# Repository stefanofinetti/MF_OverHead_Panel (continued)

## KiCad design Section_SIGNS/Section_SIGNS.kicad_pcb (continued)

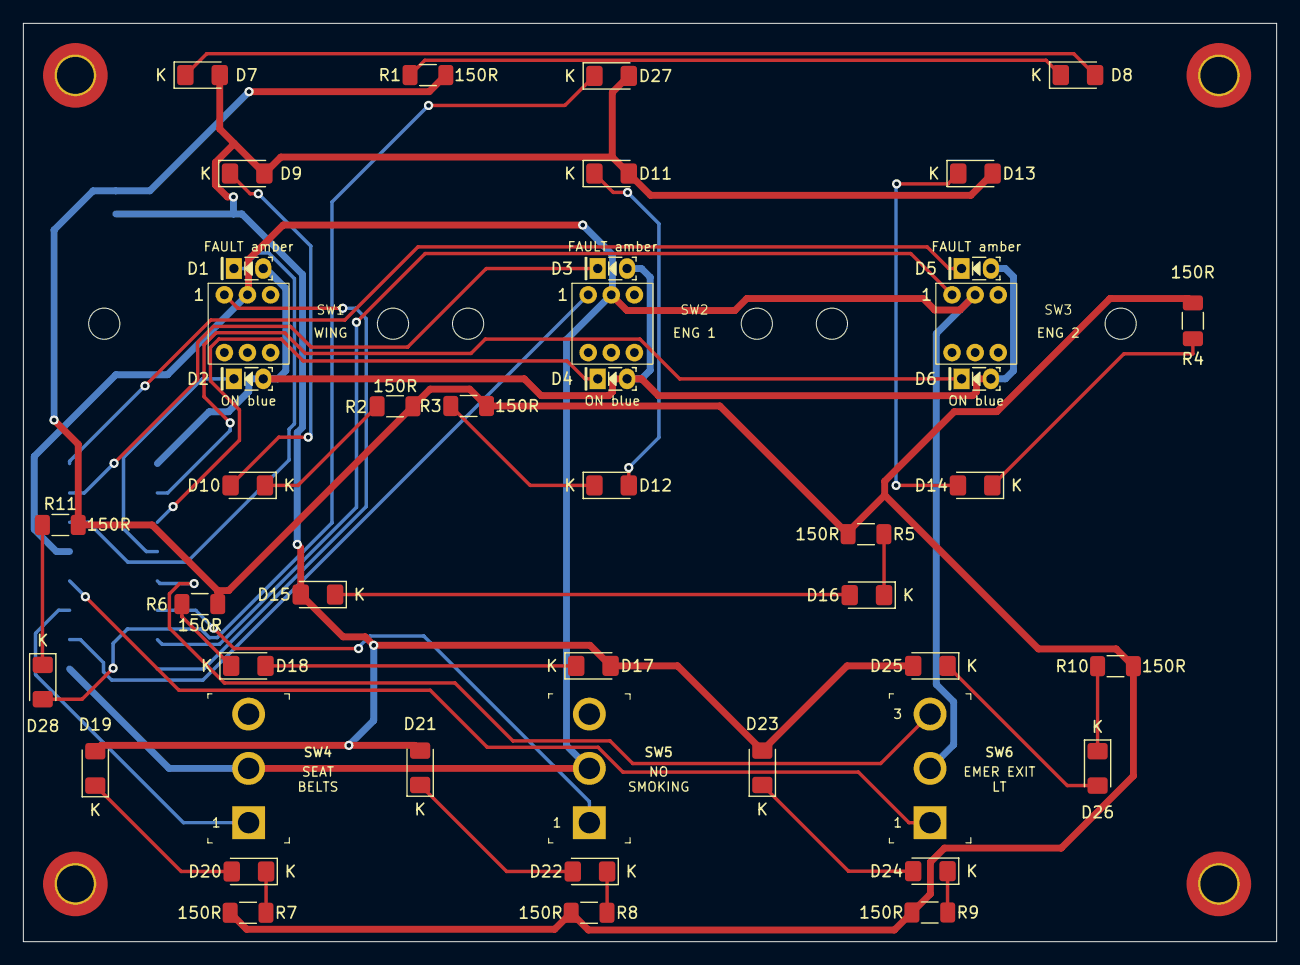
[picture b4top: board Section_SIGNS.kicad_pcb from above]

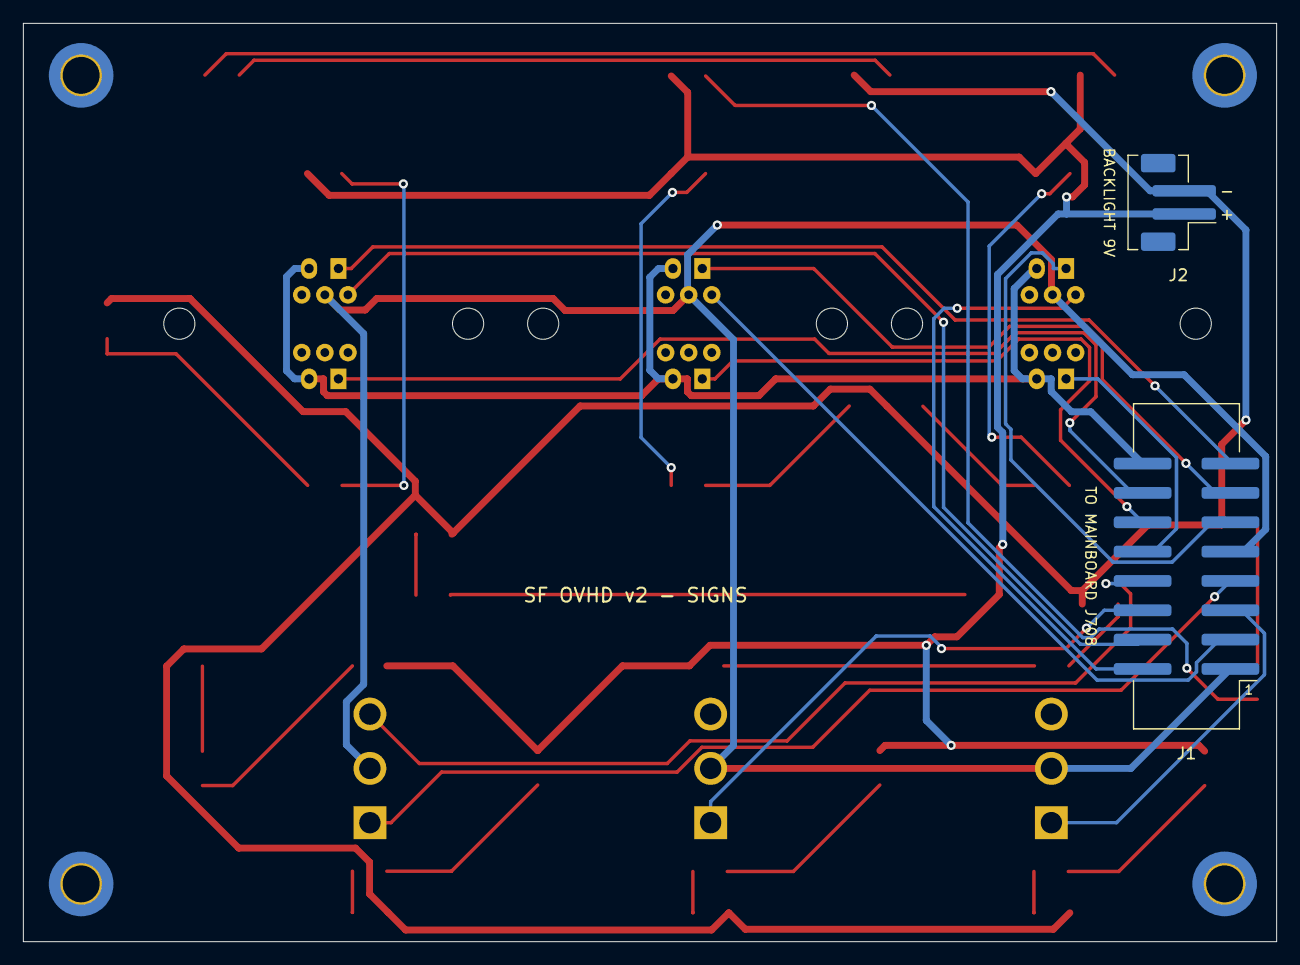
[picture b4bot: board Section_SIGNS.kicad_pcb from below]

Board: 2 copper layers, 108.5 x 79.5 mm, 57 parts (2 on the bottom side), 39 nets.

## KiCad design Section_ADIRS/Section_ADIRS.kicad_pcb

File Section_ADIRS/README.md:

# ADIRS section board (v2)

The v2 board under the ADIRS panel. It carries the panel's switches, annunciator LEDs and backlight, at their v1 positions, and reaches the mainboard through one ribbon and one pair of backlight wires. There are no ICs on it. The design rules shared by the eight section boards are in [`docs/board-split.md`](../docs/board-split.md).

* **PCB:** 132.5 × 81.5 mm, 2 layers, 1.6 mm. Every v1 hole is kept.
* **Status:** routed with Freerouting. ERC, DRC and schematic parity are clean. Not yet ordered.

**Top**, the panel side:

**Bottom**, with the connectors:

Rendered by KiCad from the board file. The bottom is seen from below, so it is mirrored against the top. The ADR rotaries have no 3D model yet and show as pads only.

## Connectors

Both are new on v2 and sit on the **back**, so nothing new stands proud of the front.

| Ref | What | Goes to |
|---|---|---|
| J1 | Shrouded IDC header, 20 pins, SMD | J701 on the mainboard, straight ribbon, pin 1 to pin 1 |
| J2 | JST PH, 2 pins, SMD. Pin 1 `+9V_BL` (`+`), pin 2 the switched return (`−`) | screw terminal J601 on the mainboard |

J1 and J2 are on the back between ADR 1 and ADR 3.

The signal on every ribbon pin is in the design document: [ADIRS — 20 pins](../docs/board-split.md#adirs--20-pins).

## Switches

| Ref | Switch | Type | v1 ref |
|---|---|---|---|
| SW1 | ADIRS ADR 1 | ADR rotary | SW25 |
| SW2 | ADIRS ADR 3 | ADR rotary | SW26 |
| SW3 | ADIRS ADR 2 | ADR rotary | SW27 |
| SW4 | ADIRS GND CTL | Korry | SW24 |

## Annunciators

Anodes on `+5V_LED` from the ribbon, cathodes back down the ribbon to their TLC5927 output. No resistors: the TLC5927 sets the current.

| Ref | Colour | Legend | Chain bit | Driver | v1 ref |
|---|---|---|---|---|---|
| D1 | blue | `GND_CTL_ON` | `ANN_LOWER` 16 | U502 (v1 U7) | D109 |

## Backlight

18 LEDs, 1206 (D2–D19), on 9 V, in 9 strings of two with 150 Ω (R1–R9). Each string runs at about 17 mA. `K` marks every cathode on the silkscreen.

## Assembly notes

* **SW2, in the middle, is IR 3, and SW3, on the right, is IR 2**, as on the A320 (IR 1, IR 3, IR 2 from left to right) and in the `.mfmc`. The v1 footprints were labelled the other way round; the copper decides.
* Rotary positions: 1 OFF, 2 NAV, 3 ATT; common on pin 9, to GND.
* J3 is the ADIRS OLED socket, where it was on v1: 1 GND, 2 +3V3, 3 SCL, 4 SDA, on PCA9548A channel 2.
* GND CTL is on this board because that is where it sits under the printed panel.
* There is no 3D model of the ADR rotary yet, so the render shows only its pads.
* Every part has its value, polarity or pin 1 on the silkscreen of its own side. Each part's description in the schematic names its v1 reference.

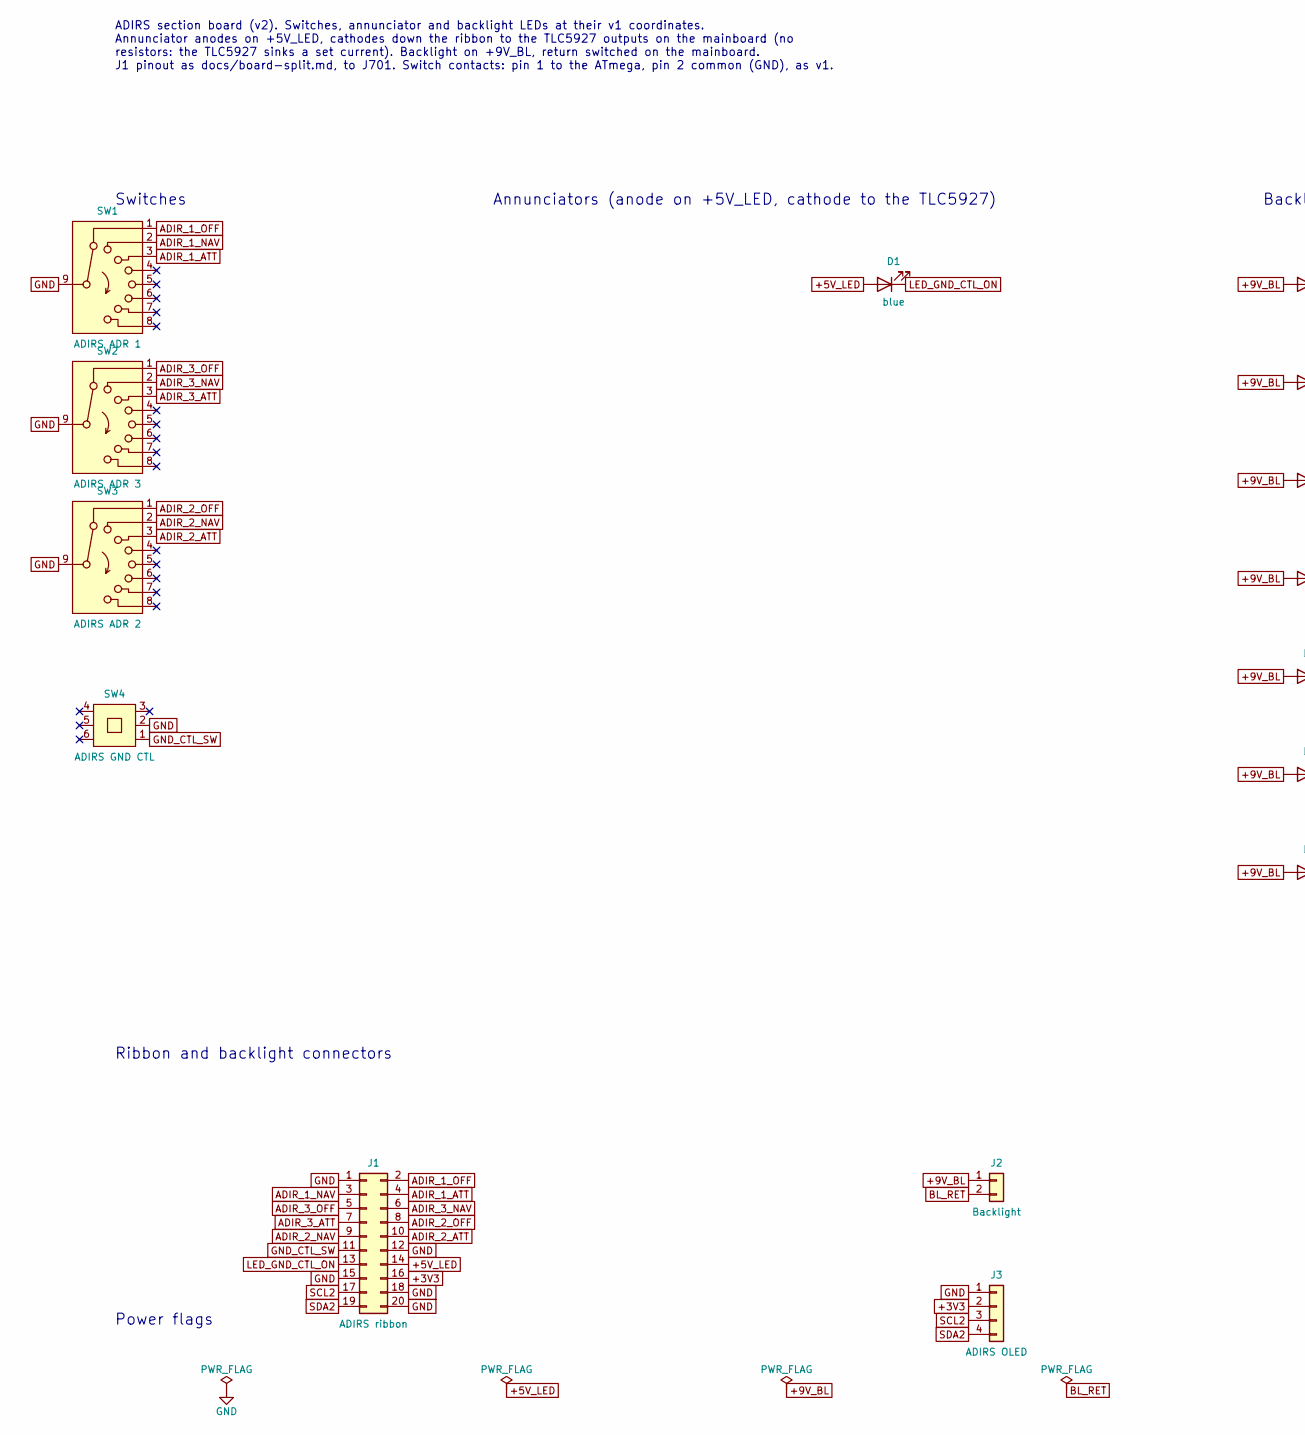
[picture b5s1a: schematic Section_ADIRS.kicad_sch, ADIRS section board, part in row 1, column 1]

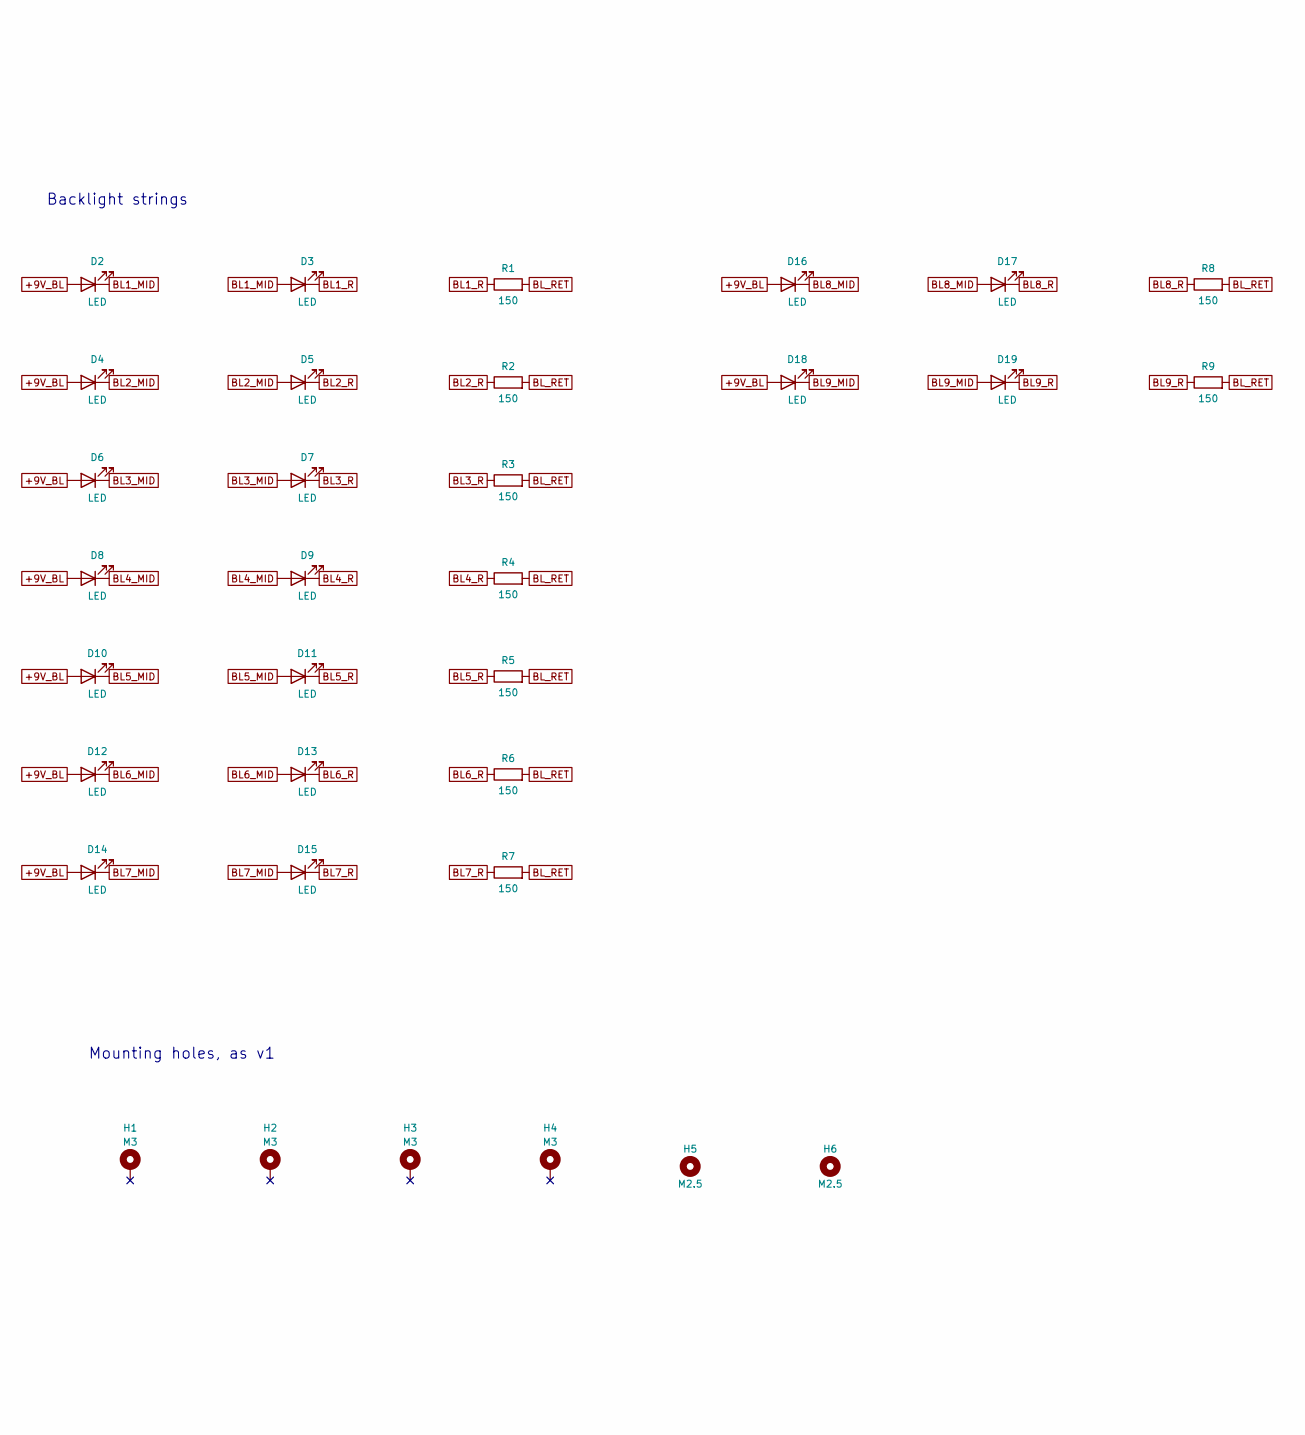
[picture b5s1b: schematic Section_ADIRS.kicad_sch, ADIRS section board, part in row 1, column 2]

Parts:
D1: blue; LED_Rectangular_W3.9mm_H1.8mm_FlatTop
D2, D3, D4, D5, D6, D7, D8, D9, D10, D11, D12, D13, D14, D15, D16, D17, D18, D19: LED; LED_1206_3216Metric_Pad1.42x1.75mm_HandSolder
H1, H2, H3, H4: M3; MountingHole_3.2mm_M3_DIN965_Pad_TopBottom
H5, H6: M2.5; MountingHole_2.7mm_M2.5
J1: ADIRS ribbon; IDC-Header_2x10_P2.54mm_Vertical_SMD
J2: Backlight; JST_PH_B2B-PH-SM4-TB_1x02-1MP_P2.00mm_Vertical
J3: ADIRS OLED; PinSocket_1x04_P2.54mm_Vertical
R1, R2, R3, R4, R5, R6, R7, R8, R9: 150; R_1206_3216Metric_Pad1.30x1.75mm_HandSolder
SW1: ADIRS ADR 1; Rotary_SW_8x1_SF
SW2: ADIRS ADR 3; Rotary_SW_8x1_SF
SW3: ADIRS ADR 2; Rotary_SW_8x1_SF
SW4: ADIRS GND CTL; G-Switch_PS-7054DVB-6PN

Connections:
+3V3: J1.16, J3.2
+5V_LED: D1.2 (A), J1.14
+9V_BL: D2.2 (A), D4.2 (A), D6.2 (A), D8.2 (A), D10.2 (A), D12.2 (A), D14.2 (A), D16.2 (A), D18.2 (A), J2.1
ADIR_1_ATT: J1.4, SW1.3
ADIR_1_NAV: J1.3, SW1.2
ADIR_1_OFF: J1.2, SW1.1
ADIR_2_ATT: J1.10, SW3.3
ADIR_2_NAV: J1.9, SW3.2
ADIR_2_OFF: J1.8, SW3.1
ADIR_3_ATT: J1.7, SW2.3
ADIR_3_NAV: J1.6, SW2.2
ADIR_3_OFF: J1.5, SW2.1
BL1_MID: D2.1 (K), D3.2 (A)
BL1_R: D3.1 (K), R1.1
BL2_MID: D4.1 (K), D5.2 (A)
BL2_R: D5.1 (K), R2.1
BL3_MID: D6.1 (K), D7.2 (A)
BL3_R: D7.1 (K), R3.1
BL4_MID: D8.1 (K), D9.2 (A)
BL4_R: D9.1 (K), R4.1
BL5_MID: D10.1 (K), D11.2 (A)
BL5_R: D11.1 (K), R5.1
BL6_MID: D12.1 (K), D13.2 (A)
BL6_R: D13.1 (K), R6.1
BL7_MID: D14.1 (K), D15.2 (A)
BL7_R: D15.1 (K), R7.1
BL8_MID: D16.1 (K), D17.2 (A)
BL8_R: D17.1 (K), R8.1
BL9_MID: D18.1 (K), D19.2 (A)
BL9_R: D19.1 (K), R9.1
BL_RET: J2.2, R1.2, R2.2, R3.2, R4.2, R5.2, R6.2, R7.2, R8.2, R9.2
GND: J1.1, J1.12, J1.15, J1.18, J1.20, J3.1, SW1.9, SW2.9, SW3.9, SW4.2
GND_CTL_SW: J1.11, SW4.1
LED_GND_CTL_ON: D1.1 (K), J1.13
SCL2: J1.17, J3.3
SDA2: J1.19, J3.4

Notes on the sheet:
Ribbon and backlight connectors
Switches
Backlight strings
ADIRS section board (v2). Switches, annunciator and backlight LEDs at their v1 coordinates. Annunciator anodes on +5V_LED, cathodes down the ribbon to the TLC5927 outputs on the mainboard (no resistors: the TLC5927 sinks a set current). Backlight on +9V_BL, return switched on the mainboard. J1 pino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
Annunciators (anode on +5V_LED, cathode to the TLC5927)
Power flags
Mounting holes, as v1

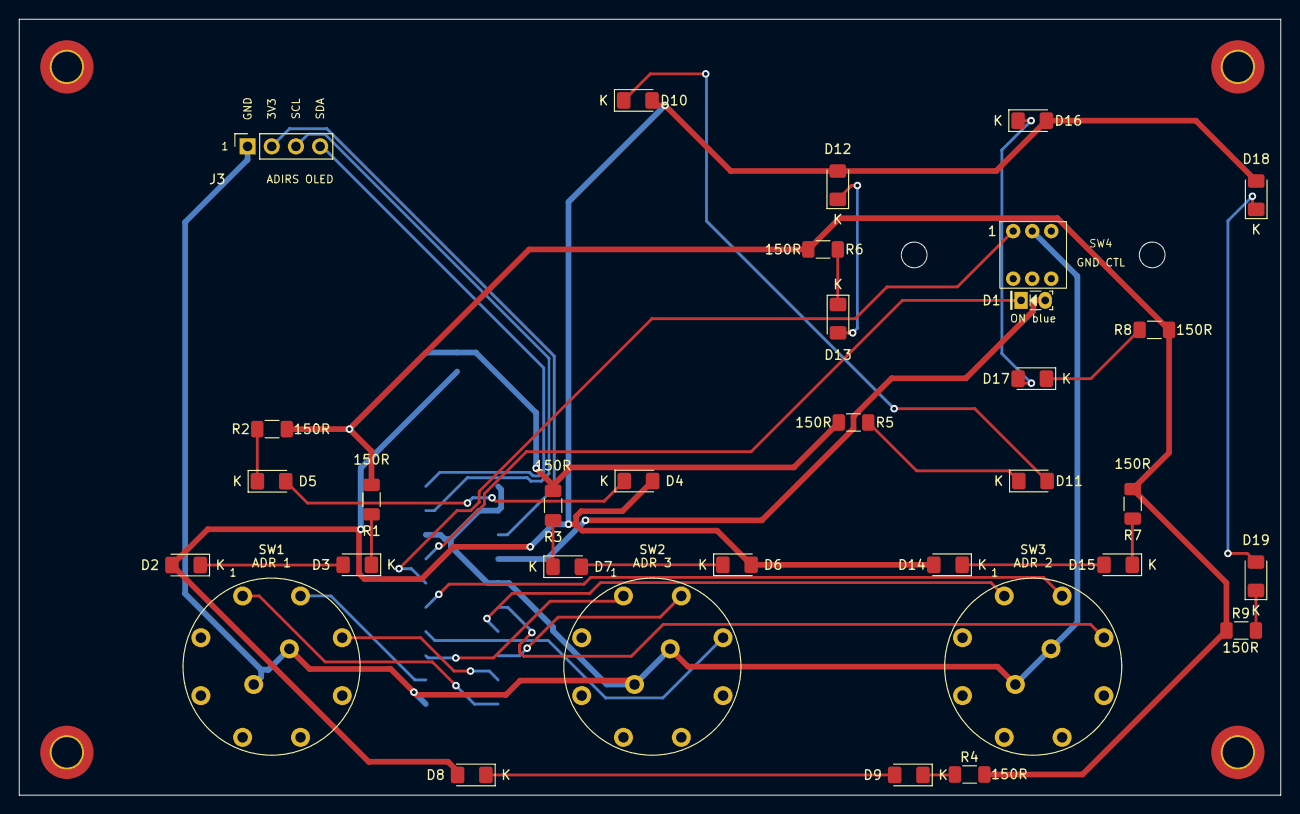
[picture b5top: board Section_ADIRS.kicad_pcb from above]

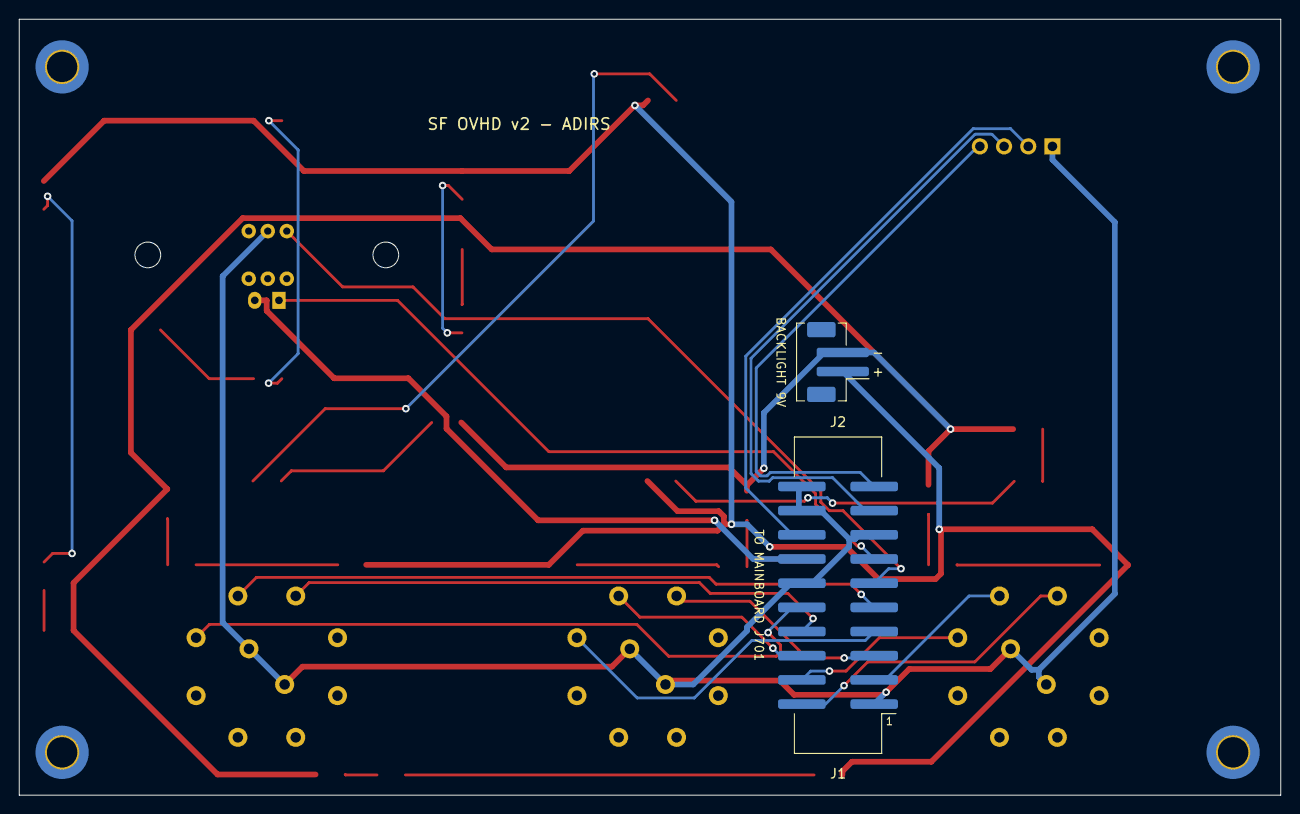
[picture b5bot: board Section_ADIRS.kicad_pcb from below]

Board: 2 copper layers, 132.5 x 81.5 mm, 41 parts (2 on the bottom side), 36 nets.

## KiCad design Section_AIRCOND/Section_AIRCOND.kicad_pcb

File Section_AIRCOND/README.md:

# AIR COND section board (v2)

The v2 board under the AIR COND panel. It carries the panel's switches, annunciator LEDs and backlight, at their v1 positions, and reaches the mainboard through one ribbon and one pair of backlight wires. There are no ICs on it. The design rules shared by the eight section boards are in [`docs/board-split.md`](../docs/board-split.md).

* **PCB:** 150.5 × 39 mm, 2 layers, 1.6 mm. Every v1 hole is kept.
* **Status:** routed with Freerouting. ERC, DRC and schematic parity are clean. Not yet ordered.

**Top**, the panel side:

**Bottom**, with the connectors:

Rendered by KiCad from the board file. The bottom is seen from below, so it is mirrored against the top.

## Connectors

Both are new on v2 and sit on the **back**, so nothing new stands proud of the front.

| Ref | What | Goes to |
|---|---|---|
| J1 | Shrouded IDC header, 16 pins, SMD | J705 on the mainboard, straight ribbon, pin 1 to pin 1 |
| J2 | JST PH, 2 pins, SMD. Pin 1 `+9V_BL` (`+`), pin 2 the switched return (`−`) | screw terminal J605 on the mainboard |

J1 and J2 are along the top edge on the left, the side nearest the mainboard.

The signal on every ribbon pin is in the design document: [AIR COND — 16 pins](../docs/board-split.md#air-cond--16-pins).

## Switches

| Ref | Switch | Type | v1 ref |
|---|---|---|---|
| SW1 | AIRCOND APU BLEED | Korry | SW10 |
| SW2 | AIRCOND PACK 1 | Korry | SW11 |
| SW3 | AIRCOND PACK 2 | Korry | SW12 |
| SW4 | AIRCOND EXT PWR | Korry | SW13 |

## Annunciators

Anodes on `+5V_LED` from the ribbon, cathodes back down the ribbon to their TLC5927 output. No resistors: the TLC5927 sets the current.

| Ref | Colour | Legend | Chain bit | Driver | v1 ref |
|---|---|---|---|---|---|
| D1 | amber | `APU_BLEED_FAULT` | `ANN_UPPER` 29 | U504 (v1 U5) | D87 |
| D2 | blue | `APU_BLEED_ON` | `ANN_LOWER` 25 | U502 (v1 U7) | D129 |
| D3 | amber | `PACK1_FAULT` | `ANN_UPPER` 30 | U504 (v1 U5) | D89 |
| D4 | white | `PACK1_OFF` | `ANN_LOWER` 8 | U501 (v1 U6) | D90 |
| D5 | amber | `PACK2_FAULT` | `ANN_UPPER` 31 | U504 (v1 U5) | D91 |
| D6 | white | `PACK2_OFF` | `ANN_LOWER` 12 | U501 (v1 U6) | D92 |
| D7 | green | `EXT_PWR_AVAIL` | `ANN_UPPER` 19 | U504 (v1 U5) | D99 |
| D8 | blue | `EXT_PWR_ON` | `ANN_LOWER` 21 | U502 (v1 U7) | D126 |

## Backlight

13 LEDs, 1206 (D9–D21), on 9 V: 6 strings of two with 150 Ω, and one single LED with R7, 330 Ω. Each string runs at about 17 mA. `K` marks every cathode on the silkscreen.

## Assembly notes

* D21 is a single-LED string: on v1 it was paired with D141, now on SIGNS. Its resistor R7 (v1 R76) stays where it was, but is **330 Ω, not 150 Ω**.
* EXT PWR is on this board because that is where it sits under the printed panel.
* v1 R57, which sat on this side of the seam, belongs to an ELEC string and has moved there.
* Every part has its value, polarity or pin 1 on the silkscreen of its own side. Each part's description in the schematic names its v1 reference.

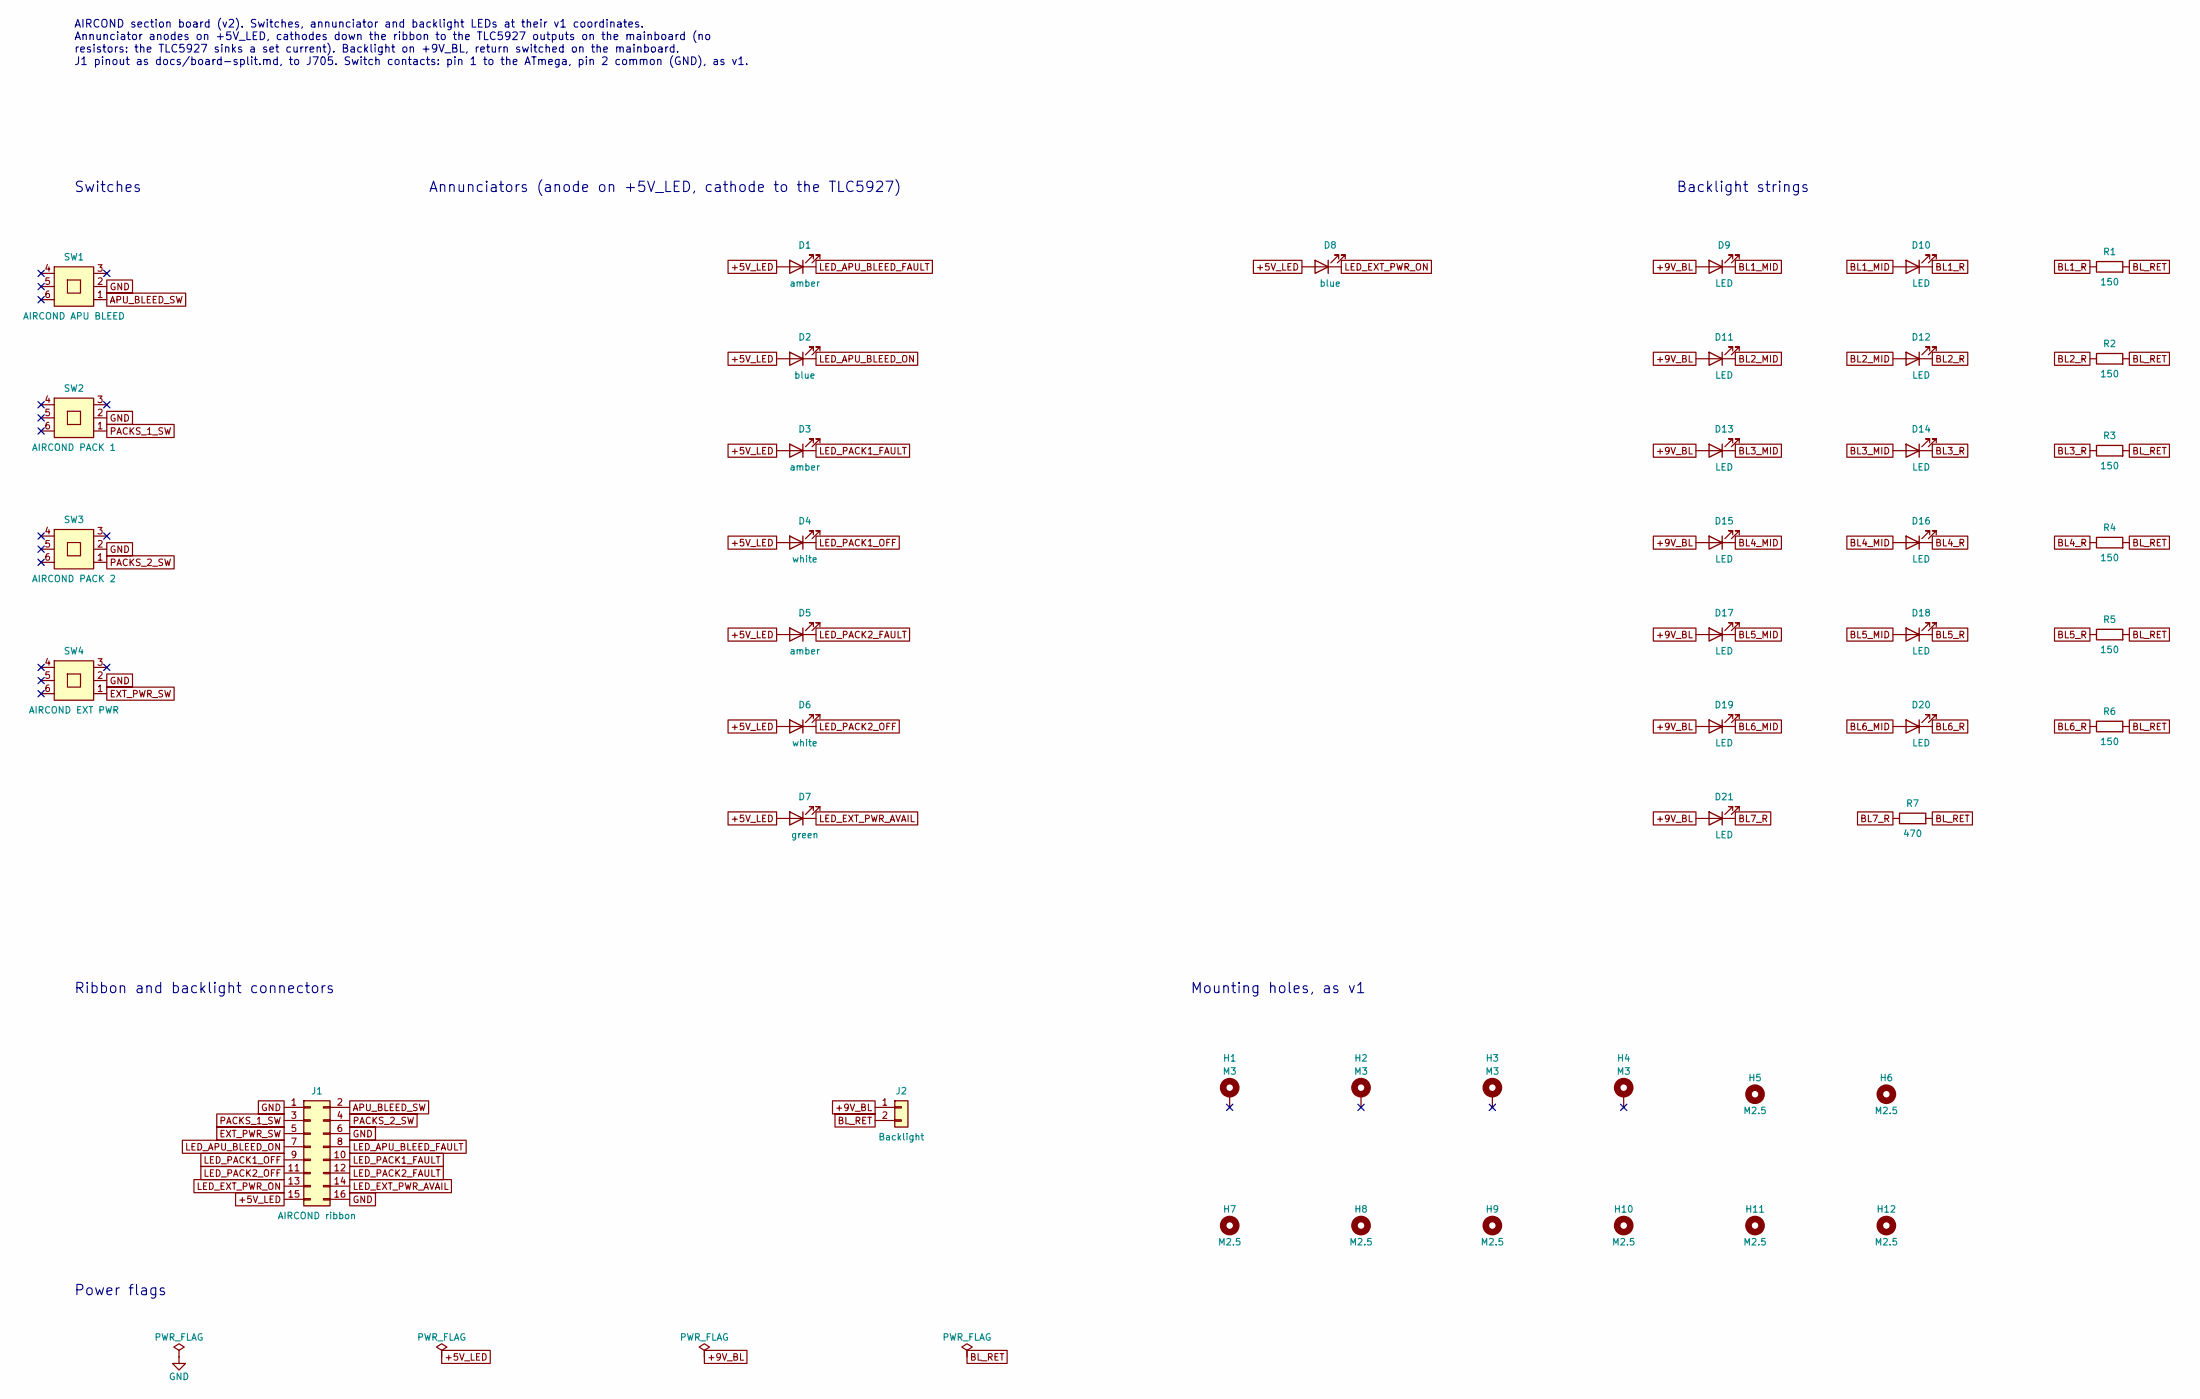
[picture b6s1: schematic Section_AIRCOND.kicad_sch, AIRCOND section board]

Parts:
D1, D3, D5: amber; LED_Rectangular_W3.9mm_H1.8mm_FlatTop
D2, D8: blue; LED_Rectangular_W3.9mm_H1.8mm_FlatTop
D4, D6: white; LED_Rectangular_W3.9mm_H1.8mm_FlatTop
D7: green; LED_Rectangular_W3.9mm_H1.8mm_FlatTop
D9, D10, D11, D12, D13, D14, D15, D16, D17, D18, D19, D20, D21: LED; LED_1206_3216Metric_Pad1.42x1.75mm_HandSolder
H1, H2, H3, H4: M3; MountingHole_3.2mm_M3_DIN965_Pad_TopBottom
H5, H6, H7, H8, H9, H10, H11, H12: M2.5; MountingHole_2.7mm_M2.5
J1: AIRCOND ribbon; IDC-Header_2x08_P2.54mm_Vertical_SMD
J2: Backlight; JST_PH_B2B-PH-SM4-TB_1x02-1MP_P2.00mm_Vertical
R1, R2, R3, R4, R5, R6: 150; R_1206_3216Metric_Pad1.30x1.75mm_HandSolder
R7: 470; R_1206_3216Metric_Pad1.30x1.75mm_HandSolder
SW1: AIRCOND APU BLEED; G-Switch_PS-7054DVB-6PN
SW2: AIRCOND PACK 1; G-Switch_PS-7054DVB-6PN
SW3: AIRCOND PACK 2; G-Switch_PS-7054DVB-6PN
SW4: AIRCOND EXT PWR; G-Switch_PS-7054DVB-6PN

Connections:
+5V_LED: D1.2 (A), D2.2 (A), D3.2 (A), D4.2 (A), D5.2 (A), D6.2 (A), D7.2 (A), D8.2 (A), J1.15
+9V_BL: D9.2 (A), D11.2 (A), D13.2 (A), D15.2 (A), D17.2 (A), D19.2 (A), D21.2 (A), J2.1
APU_BLEED_SW: J1.2, SW1.1
BL1_MID: D9.1 (K), D10.2 (A)
BL1_R: D10.1 (K), R1.1
BL2_MID: D11.1 (K), D12.2 (A)
BL2_R: D12.1 (K), R2.1
BL3_MID: D13.1 (K), D14.2 (A)
BL3_R: D14.1 (K), R3.1
BL4_MID: D15.1 (K), D16.2 (A)
BL4_R: D16.1 (K), R4.1
BL5_MID: D17.1 (K), D18.2 (A)
BL5_R: D18.1 (K), R5.1
BL6_MID: D19.1 (K), D20.2 (A)
BL6_R: D20.1 (K), R6.1
BL7_R: D21.1 (K), R7.1
BL_RET: J2.2, R1.2, R2.2, R3.2, R4.2, R5.2, R6.2, R7.2
EXT_PWR_SW: J1.5, SW4.1
GND: J1.1, J1.6, J1.16, SW1.2, SW2.2, SW3.2, SW4.2
LED_APU_BLEED_FAULT: D1.1 (K), J1.8
LED_APU_BLEED_ON: D2.1 (K), J1.7
LED_EXT_PWR_AVAIL: D7.1 (K), J1.14
LED_EXT_PWR_ON: D8.1 (K), J1.13
LED_PACK1_FAULT: D3.1 (K), J1.10
LED_PACK1_OFF: D4.1 (K), J1.9
LED_PACK2_FAULT: D5.1 (K), J1.12
LED_PACK2_OFF: D6.1 (K), J1.11
PACKS_1_SW: J1.3, SW2.1
PACKS_2_SW: J1.4, SW3.1

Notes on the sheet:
Power flags
AIRCOND section board (v2). Switches, annunciator and backlight LEDs at their v1 coordinates. Annunciator anodes on +5V_LED, cathodes down the ribbon to the TLC5927 outputs on the mainboard (no resistors: the TLC5927 sinks a set current). Backlight on +9V_BL, return switched on the mainboard. J1 pi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
Switches
Annunciators (anode on +5V_LED, cathode to the TLC5927)
Backlight strings
Mounting holes, as v1
Ribbon and backlight connectors

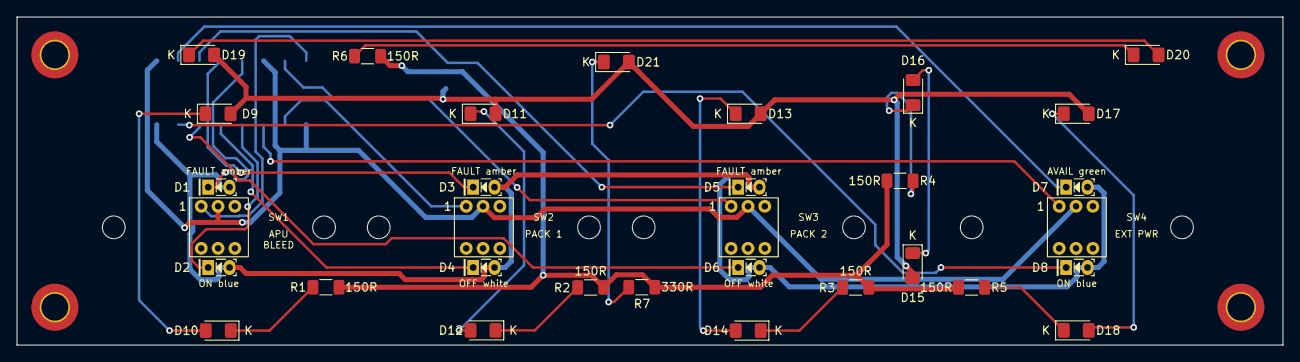
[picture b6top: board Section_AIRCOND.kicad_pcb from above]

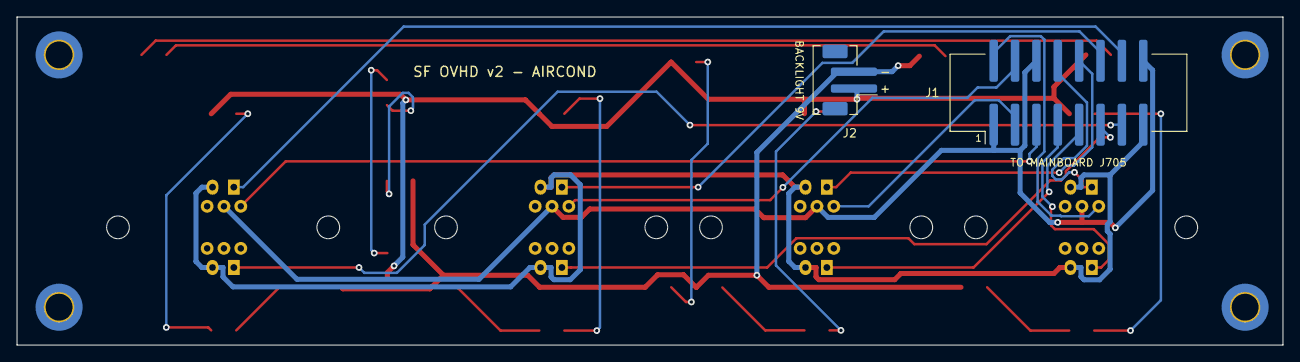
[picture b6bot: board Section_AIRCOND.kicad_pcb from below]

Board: 2 copper layers, 150.5 x 39.0 mm, 46 parts (2 on the bottom side), 29 nets.

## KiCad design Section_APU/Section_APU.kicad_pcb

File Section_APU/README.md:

# APU section board (v2)

The v2 board under the APU panel. It carries the panel's switches, annunciator LEDs and backlight, at their v1 positions, and reaches the mainboard through one ribbon and one pair of backlight wires. There are no ICs on it. The design rules shared by the eight section boards are in [`docs/board-split.md`](../docs/board-split.md).

* **PCB:** 39 × 79.5 mm, 2 layers, 1.6 mm. Every v1 hole is kept.
* **Status:** routed with Freerouting. ERC, DRC and schematic parity are clean. Not yet ordered.

| Top: the panel side | Bottom: the connectors |
|---|---|
|  |  |

Rendered by KiCad from the board file. The bottom is seen from below, so it is mirrored against the top.

## Connectors

Both are new on v2 and sit on the **back**, so nothing new stands proud of the front.

| Ref | What | Goes to |
|---|---|---|
| J1 | Shrouded IDC header, 10 pins, SMD | J707 on the mainboard, straight ribbon, pin 1 to pin 1 |
| J2 | JST PH, 2 pins, SMD. Pin 1 `+9V_BL` (`+`), pin 2 the switched return (`−`) | screw terminal J607 on the mainboard |

J1 and J2 are on the left edge, towards the mainboard.

The signal on every ribbon pin is in the design document: [APU — 10 pins](../docs/board-split.md#apu--10-pins).

## Switches

| Ref | Switch | Type | v1 ref |
|---|---|---|---|
| SW1 | APU MASTER SW | Korry | SW1 |
| SW2 | APU START | Korry | SW2 |

## Annunciators

Anodes on `+5V_LED` from the ribbon, cathodes back down the ribbon to their TLC5927 output. No resistors: the TLC5927 sets the current.

| Ref | Colour | Legend | Chain bit | Driver | v1 ref |
|---|---|---|---|---|---|
| D1 | amber | `APU_MASTER_FAULT` | `ANN_UPPER` 23 | U504 (v1 U5) | D178 |
| D2 | blue | `APU_MASTER_ON` | `ANN_LOWER` 17 | U502 (v1 U7) | D130 |
| D3 | green | `APU_AVAIL` | `ANN_UPPER` 24 | U504 (v1 U5) | D128 |
| D4 | blue | `APU_START_ON` | `ANN_LOWER` 24 | U502 (v1 U7) | D4 |

## Backlight

5 LEDs, 1206 (D5–D9), on 9 V: 2 strings of two with 150 Ω, and one single LED with R3, 330 Ω. Each string runs at about 17 mA. `K` marks every cathode on the silkscreen.

## Assembly notes

* D9 is a single-LED string: on v1 it was paired with D149, now on SIGNS. R3, 330 Ω on the back, gives it the same 17 mA as a pair on 150 Ω.
* Every part has its value, polarity or pin 1 on the silkscreen of its own side. Each part's description in the schematic names its v1 reference.

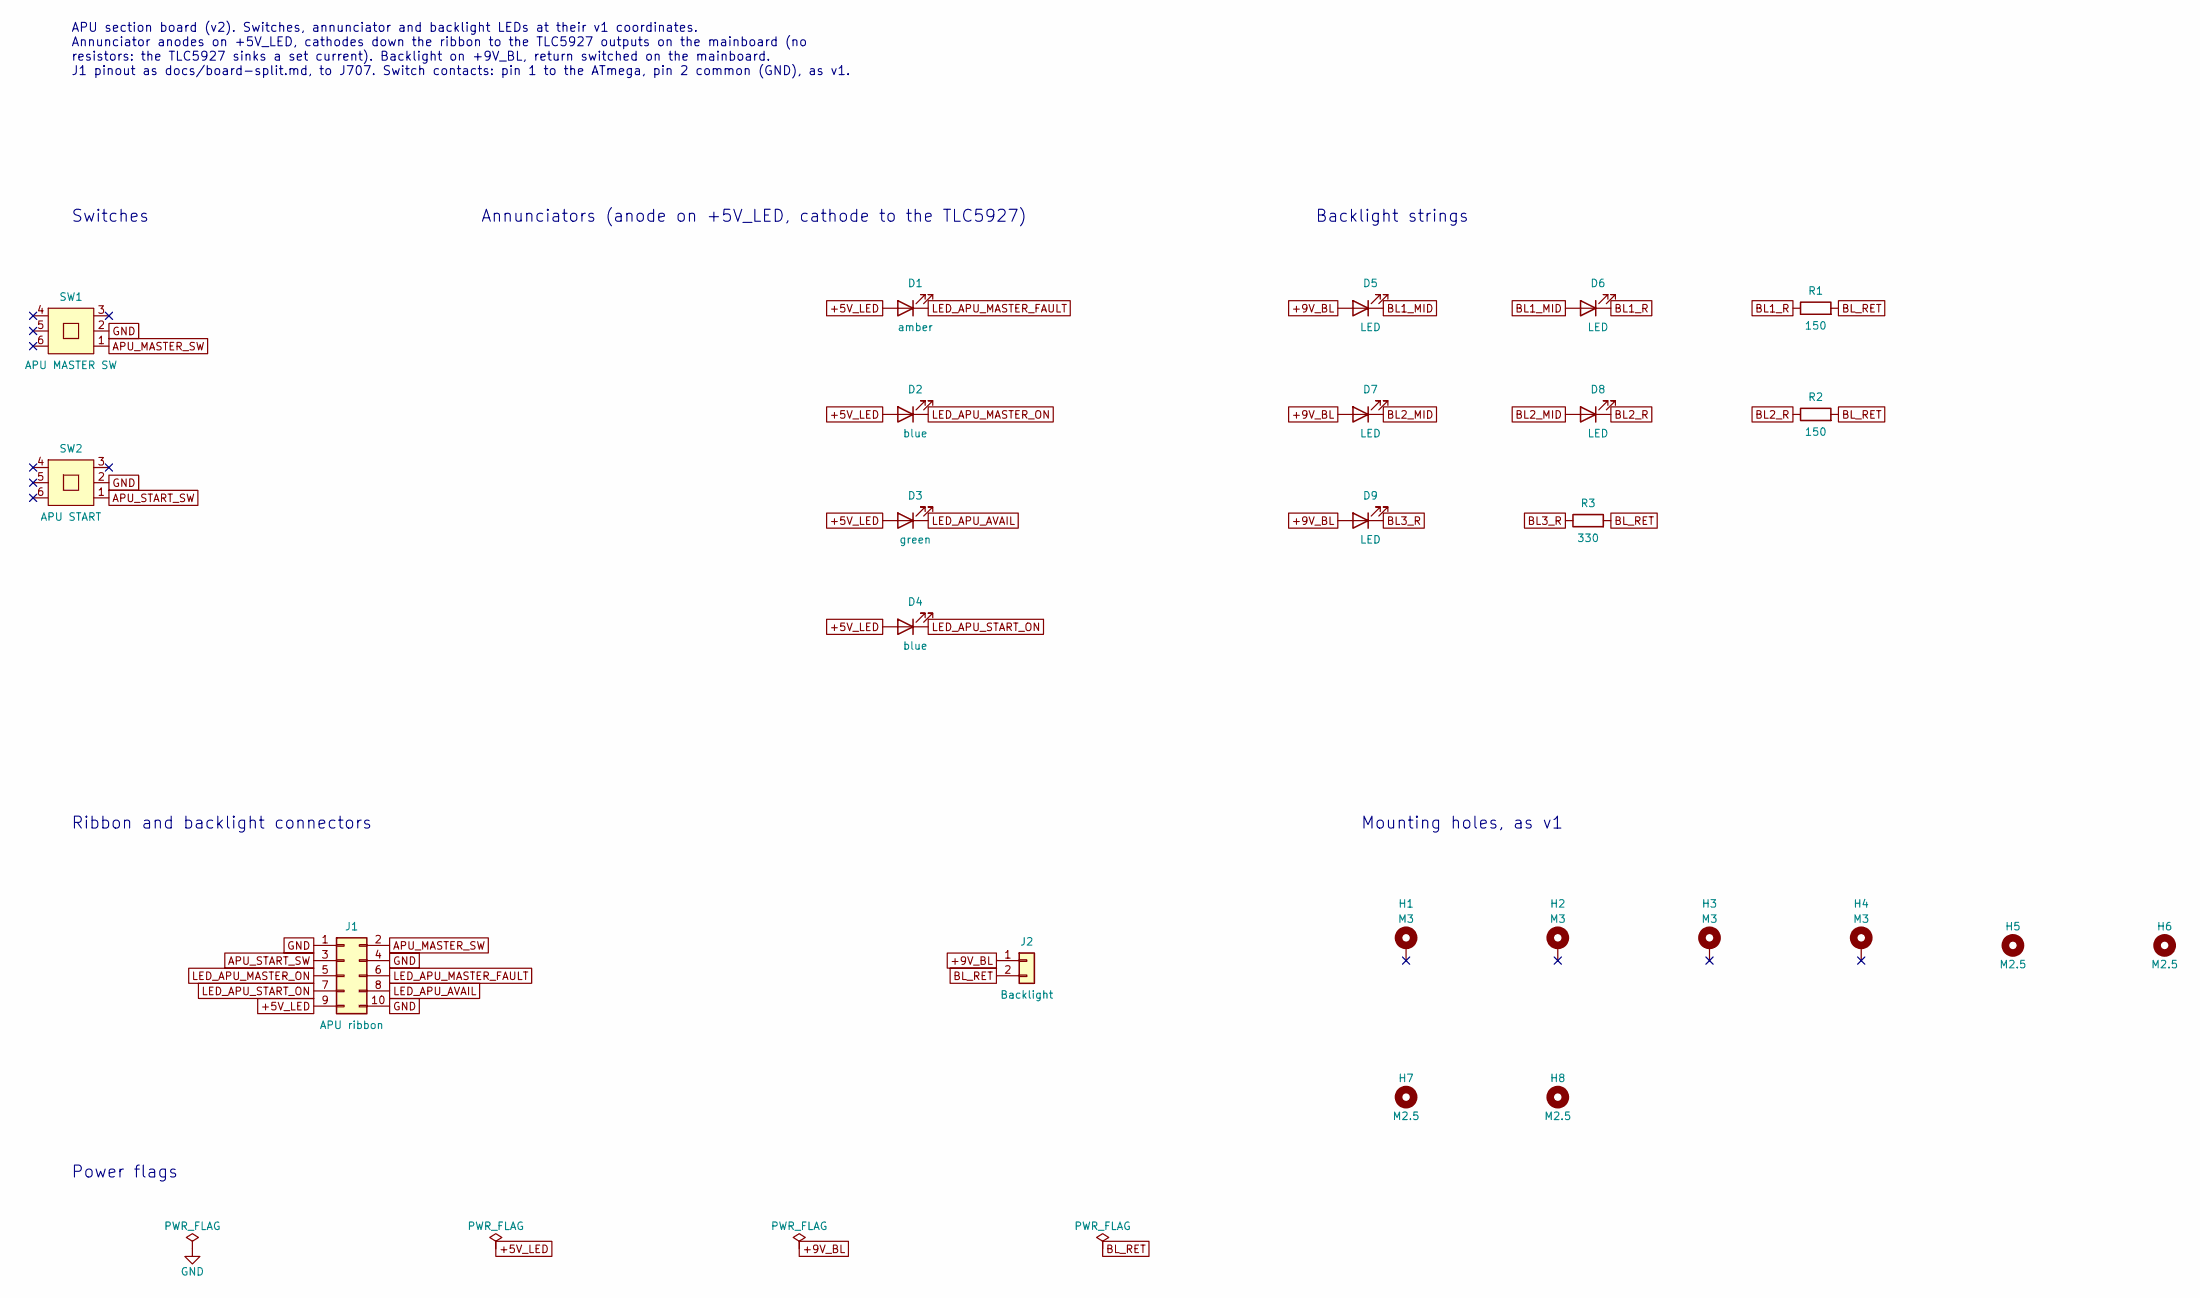
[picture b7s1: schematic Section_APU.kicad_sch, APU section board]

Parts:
D1: amber; LED_Rectangular_W3.9mm_H1.8mm_FlatTop
D2, D4: blue; LED_Rectangular_W3.9mm_H1.8mm_FlatTop
D3: green; LED_Rectangular_W3.9mm_H1.8mm_FlatTop
D5, D6, D7, D8, D9: LED; LED_1206_3216Metric_Pad1.42x1.75mm_HandSolder
H1, H2, H3, H4: M3; MountingHole_3.2mm_M3_DIN965_Pad_TopBottom
H5, H6, H7, H8: M2.5; MountingHole_2.7mm_M2.5
J1: APU ribbon; IDC-Header_2x05_P2.54mm_Vertical_SMD
J2: Backlight; JST_PH_B2B-PH-SM4-TB_1x02-1MP_P2.00mm_Vertical
R1, R2: 150; R_1206_3216Metric_Pad1.30x1.75mm_HandSolder
R3: 330; R_1206_3216Metric_Pad1.30x1.75mm_HandSolder
SW1: APU MASTER SW; G-Switch_PS-7054DVB-6PN
SW2: APU START; G-Switch_PS-7054DVB-6PN

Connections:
+5V_LED: D1.2 (A), D2.2 (A), D3.2 (A), D4.2 (A), J1.9
+9V_BL: D5.2 (A), D7.2 (A), D9.2 (A), J2.1
APU_MASTER_SW: J1.2, SW1.1
APU_START_SW: J1.3, SW2.1
BL1_MID: D5.1 (K), D6.2 (A)
BL1_R: D6.1 (K), R1.1
BL2_MID: D7.1 (K), D8.2 (A)
BL2_R: D8.1 (K), R2.1
BL3_R: D9.1 (K), R3.1
BL_RET: J2.2, R1.2, R2.2, R3.2
GND: J1.1, J1.4, J1.10, SW1.2, SW2.2
LED_APU_AVAIL: D3.1 (K), J1.8
LED_APU_MASTER_FAULT: D1.1 (K), J1.6
LED_APU_MASTER_ON: D2.1 (K), J1.5
LED_APU_START_ON: D4.1 (K), J1.7

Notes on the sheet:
Ribbon and backlight connectors
Annunciators (anode on +5V_LED, cathode to the TLC5927)
APU section board (v2). Switches, annunciator and backlight LEDs at their v1 coordinates. Annunciator anodes on +5V_LED, cathodes down the ribbon to the TLC5927 outputs on the mainboard (no resistors: the TLC5927 sinks a set current). Backlight on +9V_BL, return switched on the mainboard. J1 pinout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
Switches
Backlight strings
Mounting holes, as v1
Power flags
